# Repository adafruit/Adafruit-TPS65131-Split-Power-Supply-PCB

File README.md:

## Adafruit TPS65131 Split Power Supply Boost Converter - +6 ~ 15 / -6V ~ -15V PCB

<a href="http://www.adafruit.com/products/6280"><br/>
Click here to purchase one from the Adafruit shop</a>

PCB files for the Adafruit TPS65131 Split Power Supply Boost Converter - +6~15 / -6V~-15V. 

Format is EagleCAD schematic and board layout
* https://www.adafruit.com/product/6280

### Description

Need those tricky split-rail voltages for your vintage electronics? The Adafruit TPS65131 Split Rail Boost Converter generates both positive and negative voltage rails from a single 3-5V input. This makes it great for mimicking or replacing a transformer-based power supply or something that needs negative bias. We kept the design compact, and it even has adjustable output pots, so you can tune the voltages from about +6~+15VDC and -6~15VDC. Perfect for use with audio or retro projects now that transformer supplies are hard to get, or if you want to have something that could run on battery or USB.

Features:

* The TPS65131 can generate positive and negative voltages simultaneously
* Adjustable voltage ranges: +6V to +15V and -6V to -15V, these are somewhat approximate because the trimmer pot can vary, you may find +/-0.5V variance on the bookend values
* Input voltage: 3 to 5.5V
* Output current: 150mA from each rail (assuming +12/-12V from 4.5V input). So not good for a motor, best for biasing or powering analog/digital electronics
* Compact breadboard-friendly design with mounting holes and two trimmer pots

We initially designed this to generate a -12V bias voltage on an Apple ][ disk drive, but you could definitely use it for synthesizers/modulars, TTL logic or op-amps that want a wide power supply, biasing LCDs or OLEDs, as well as other uncommon voltages. The trimmers let you tweak the outputs so you could get +6V and -12V or +12 and -8V. 

### License

Adafruit invests time and resources providing this open source design, please support Adafruit and open-source hardware by purchasing products from [Adafruit](https://www.adafruit.com)!

Designed by Limor Fried/Ladyada for Adafruit Industries.

Creative Commons Attribution/Share-Alike, all text above must be included in any redistribution. 
See license.txt for additional details.

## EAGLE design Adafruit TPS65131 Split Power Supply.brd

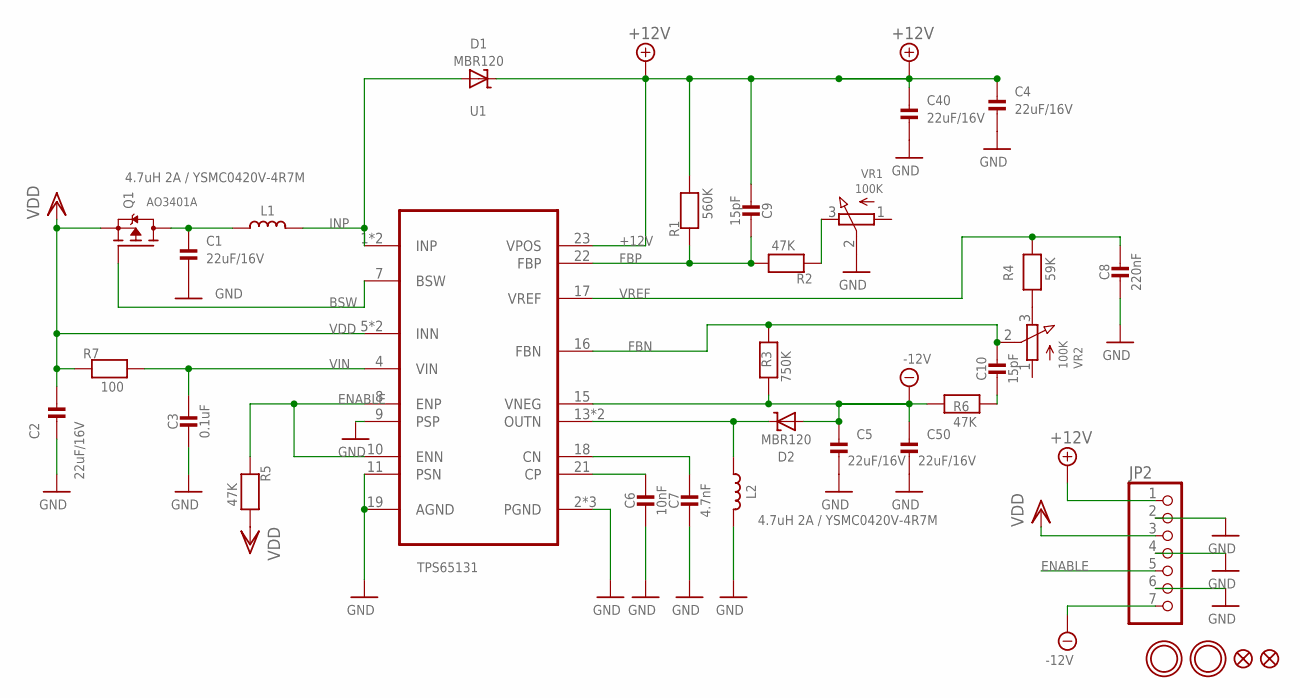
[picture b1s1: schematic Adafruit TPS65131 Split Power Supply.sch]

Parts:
C1, C2, C4, C5, C40, C50: 22uF/16V; 0805-NO
C3: 0.1uF; 0603-NO
C6: 10nF; 0603-NO
C7: 4.7nF; 0603-NO
C8: 220nF; 0603-NO
C9, C10: 15pF; 0603-NO
D1, D2: MBR120; SOD-123FL
FID1, FID2: FIDUCIAL_0.5MM
JP2: HEADER-1X7THICKER; 1X07_ROUND_76
L1, L2: 4.7uH 2A / YSMC0420V-4R7M; INDUCTOR_4X4MM_NR401
Q1: AO3401A; SOT23-WIDE
R1: 560K; 0603-NO
R2, R5, R6: 47K; 0603-NO
R3: 750K; 0603-NO
R4: 59K; 0603-NO
R7: 100; 0603-NO
U1: TPS65131; QFN24_4MM
U$1, U$2: MOUNTINGHOLE2.5; MOUNTINGHOLE_2.5_PLATED
VR1, VR2: 100K; TRIMPOT_BOURNS_TC33X-2

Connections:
+12V: C4.2, C9.1, C40.2, D1.C, JP2.1, R1.2, U1.23 (VPOS)
-12V: C5.2, C50.2, D2.A, JP2.7, R3.1, R6.1, U1.15 (VNEG)
BSW: Q1.1 (G), U1.7 (BSW)
ENABLE: JP2.5, R5.1, U1.8 (ENP), U1.10 (ENN)
FBN: C10.2, R3.2, U1.16 (FBN), VR2.2 (S)
FBP: C9.2, R1.1, R2.2, U1.22 (FBP)
GND: C1.1, C2.1, C3.1, C4.1, C5.1, C6.1, C7.1, C8.1, C40.1, C50.1, JP2.2, JP2.4, JP2.6, L2.P$2 (2), U1.2 (PGND), U1.3 (PGND), U1.9 (PSP), U1.11 (PSN), U1.19 (AGND), U1.25 (PGND), VR1.2 (S)
INP: D1.A, L1.P$2 (2), U1.1 (INP), U1.24 (INP)
unnamed: C6.2, U1.21 (CP)
unnamed: C1.2, L1.P$1 (1), Q1.3 (D)
unnamed: R2.1, VR1.3 (E)
unnamed: R4.1, VR2.3 (E)
unnamed: C10.1, R6.2
unnamed: C7.2, U1.18 (CN)
OUTN: D2.C, L2.P$1 (1), U1.13 (OUTN), U1.14 (OUTN)
VDD: C2.2, JP2.3, Q1.2 (S), R5.2, R7.1, U1.5 (INN), U1.6 (INN)
VIN: C3.2, R7.2, U1.4 (VIN)
VREF: C8.2, R4.2, U1.17 (VREF)

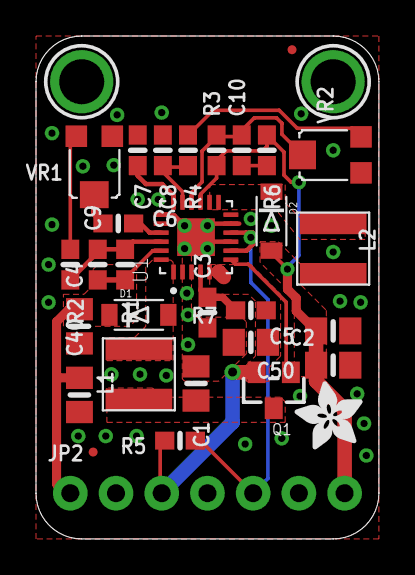
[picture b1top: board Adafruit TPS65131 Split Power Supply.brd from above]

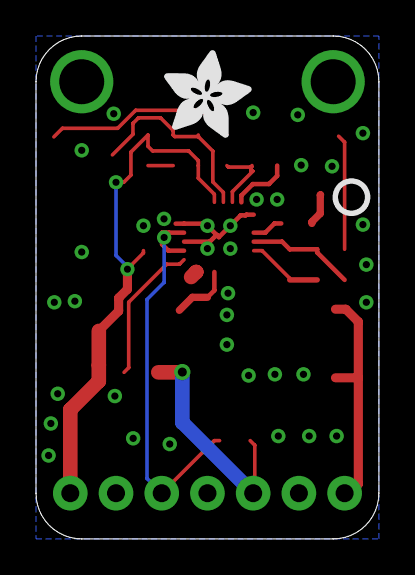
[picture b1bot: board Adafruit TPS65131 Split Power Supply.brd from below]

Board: 2 copper layers, 19.1 x 27.9 mm, 47 parts (4 on the bottom side), 18 nets.

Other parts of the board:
PLABEL0: PLABEL0
PLABEL1: PLABEL1
PLABEL2: PLABEL2
PLABEL3: PLABEL3
PLABEL4: PLABEL4
PLABEL5: PLABEL5
PLABEL6: PLABEL6
PLABEL7: PLABEL7
PLABEL8: PLABEL8
PLABEL9: PLABEL9
PLABEL10: PLABEL10
PLABEL11: PLABEL11
U$3: ADAFRUIT_3.5MM
U$4: ADAFRUIT_5MM
U$5: PCBFEAT-REV-040

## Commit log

2025-03-13 cookiecutter
